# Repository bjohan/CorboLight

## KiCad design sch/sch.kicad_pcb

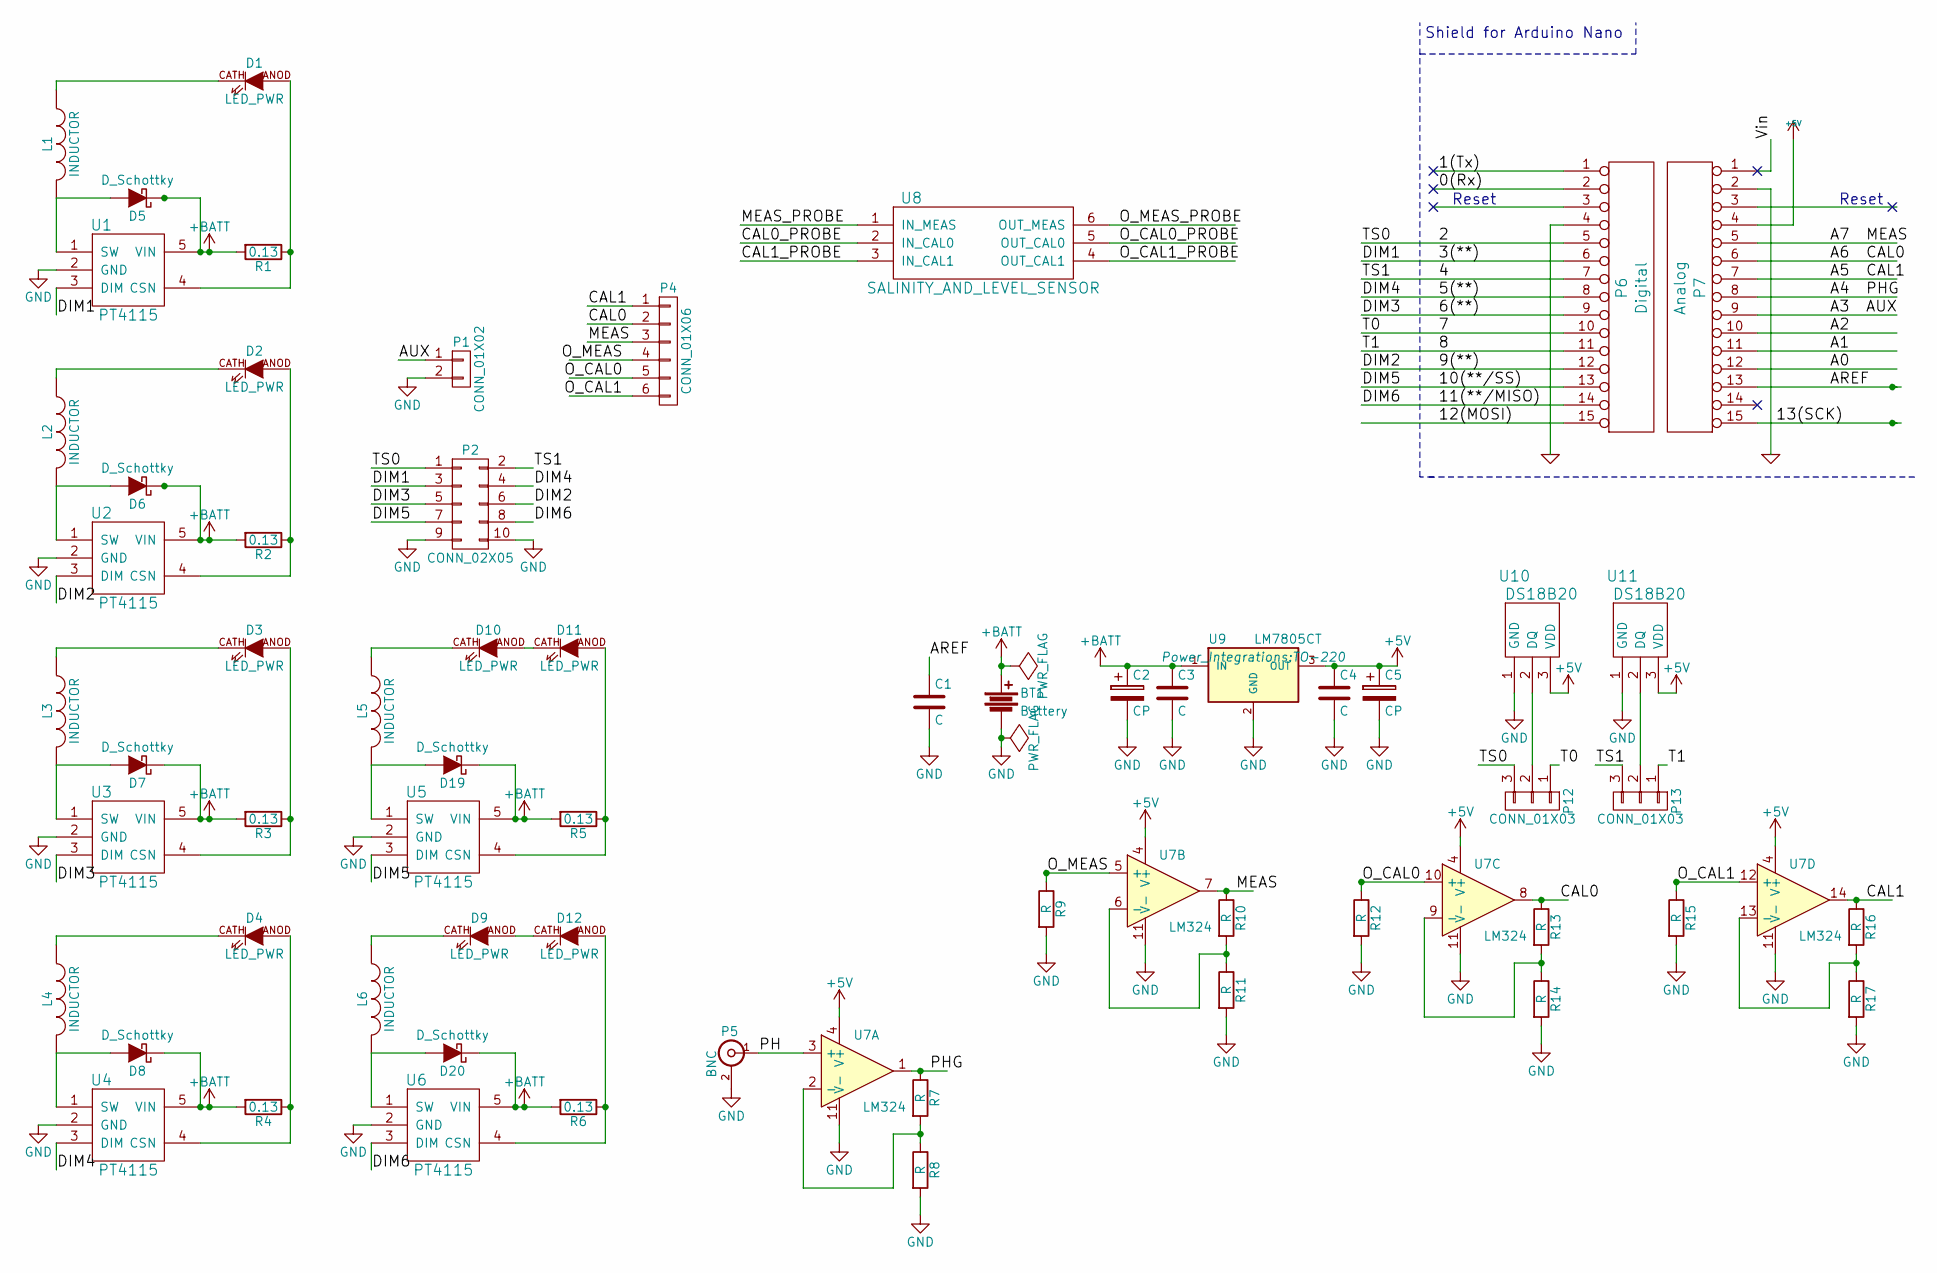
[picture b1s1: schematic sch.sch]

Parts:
BT1: Battery; bornier2
C1, C3, C4: C; C_1206_HandSoldering
C2, C5: CP; C_Radial_D5_L6_P2.5
D1, D2, D3, D4, D9, D10, D11, D12: LED_PWR; lumiled-2-LAMBERTIAN
D5, D6, D7, D8, D19, D20: D_Schottky; DO-214AB_Handsoldering
L1, L2, L3, L4, L5, L6: INDUCTOR; Neosid_Inductor_Ms95
P1: CONN_01X02; PINHEAD1-2
P2: CONN_02X05; IDC_Header_Straight_10pins
P4: CONN_01X06; PINHEAD1-6
P5: BNC; bnc-ci
P6: Digital; Socket_Strip_Arduino_1x15
P7: Analog; Socket_Strip_Arduino_1x15
P12, P13: CONN_01X03; PINHEAD1-3
R1, R2, R3, R4, R5, R6: 0.13; R_1206_HandSoldering
R7, R8, R9, R10, R11, R12, R13, R14, R15, R16, R17: R; R_0805_HandSoldering
U1, U2, U3, U4, U5, U6: PT4115; SOT89-5_Housing_Handsoldering
U7: LM324; SOIC-14_N
U8: SALINITY_AND_LEVEL_SENSOR
U9: LM7805CT; TO-220
U10, U11: DS18B20; TO-92_Inline_Narrow_Oval

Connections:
+5V: C4.1, C5.1, P7.4, U7.4 (V+), U9.3 (OUT), U10.3 (VDD), U11.3 (VDD)
+BATT: BT1.1, C2.1, C3.1, D5.1 (K), D6.1 (K), D7.1 (K), D8.1 (K), D19.1 (K), D20.1 (K), R1.2, R2.2, R3.2, R4.2, R5.2, R6.2, U1.5 (VIN), U2.5 (VIN), U3.5 (VIN), U4.5 (VIN), U5.5 (VIN), U6.5 (VIN), U9.1 (IN)
/0(Rx): P6.2
/1(Tx): P6.1
/2: P2.1, P6.5, P12.3
/3(**): P2.3, P6.6, U1.3 (DIM)
/4: P2.2, P6.7, P13.3
/5(**): P2.4, P6.8, U4.3 (DIM)
/6(**): P2.5, P6.9, U3.3 (DIM)
/7: P6.10, P12.1
/8: P6.11, P13.1
/9(**): P2.6, P6.12, U2.3 (DIM)
/10(**/SS): P2.7, P6.13, U5.3 (DIM)
/11(**/MISO): P2.8, P6.14, U6.3 (DIM)
/12(MOSI): P6.15 (p15)
/13(SCK): P7.15 (p15)
/A0: P7.12
/A1: P7.11
/A2: P7.10
/A3: P1.1, P7.9
/A4: P7.8, R7.1, U7.1
/A5: P4.1, P7.7, R16.1, U7.14
/A6: P4.2, P7.6, R13.1, U7.8
/A7: P4.3, P7.5, R10.1, U7.7
/AREF: C1.1, P7.13
/O_CAL0: P4.5, R12.1, U7.10 (+)
/O_CAL1: P4.6, R15.1, U7.12 (+)
/O_MEAS: P4.4, R9.1, U7.5 (+)
/PH: P5.1 (In), U7.3 (+)
/Vin: P7.1
GND: BT1.2, C1.2, C2.2, C3.2, C4.2, C5.2, P1.2, P2.9, P2.10, P5.2 (Ext), P6.4, P7.2, R8.2, R9.2, R11.2, R12.2, R14.2, R15.2, R17.2, U1.2 (GND), U2.2 (GND), U3.2 (GND), U4.2 (GND), U5.2 (GND), U6.2 (GND), U7.11 (V-), U9.2 (GND), U10.1 (GND), U11.1 (GND)
unnamed: D1.ANOD (A), R1.1, U1.4 (CSN)
unnamed: D1.CATH (C), L1.1
unnamed: D2.ANOD (A), R2.1, U2.4 (CSN)
unnamed: D2.CATH (C), L2.1
unnamed: D3.ANOD (A), R3.1, U3.4 (CSN)
unnamed: D3.CATH (C), L3.1
unnamed: D4.ANOD (A), R4.1, U4.4 (CSN)
unnamed: D4.CATH (C), L4.1
unnamed: D5.2 (A), L1.2, U1.1 (SW)
unnamed: D6.2 (A), L2.2, U2.1 (SW)
unnamed: D7.2 (A), L3.2, U3.1 (SW)
unnamed: D8.2 (A), L4.2, U4.1 (SW)
unnamed: D9.CATH (C), L6.1
unnamed: D10.ANOD (A), D11.CATH (C)
unnamed: D10.CATH (C), L5.1
unnamed: D11.ANOD (A), R5.1, U5.4 (CSN)
unnamed: D12.ANOD (A), R6.1, U6.4 (CSN)
unnamed: D9.ANOD (A), D12.CATH (C)
unnamed: D19.2 (A), L5.2, U5.1 (SW)
unnamed: D20.2 (A), L6.2, U6.1 (SW)
unnamed: P12.2, U10.2 (DQ)
unnamed: P13.2, U11.2 (DQ)
unnamed: R7.2, R8.1, U7.2 (-)
unnamed: R10.2, R11.1, U7.6 (-)
unnamed: R13.2, R14.1, U7.9 (-)
unnamed: R16.2, R17.1, U7.13 (-)

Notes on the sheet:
Shield for Arduino Nano
Reset

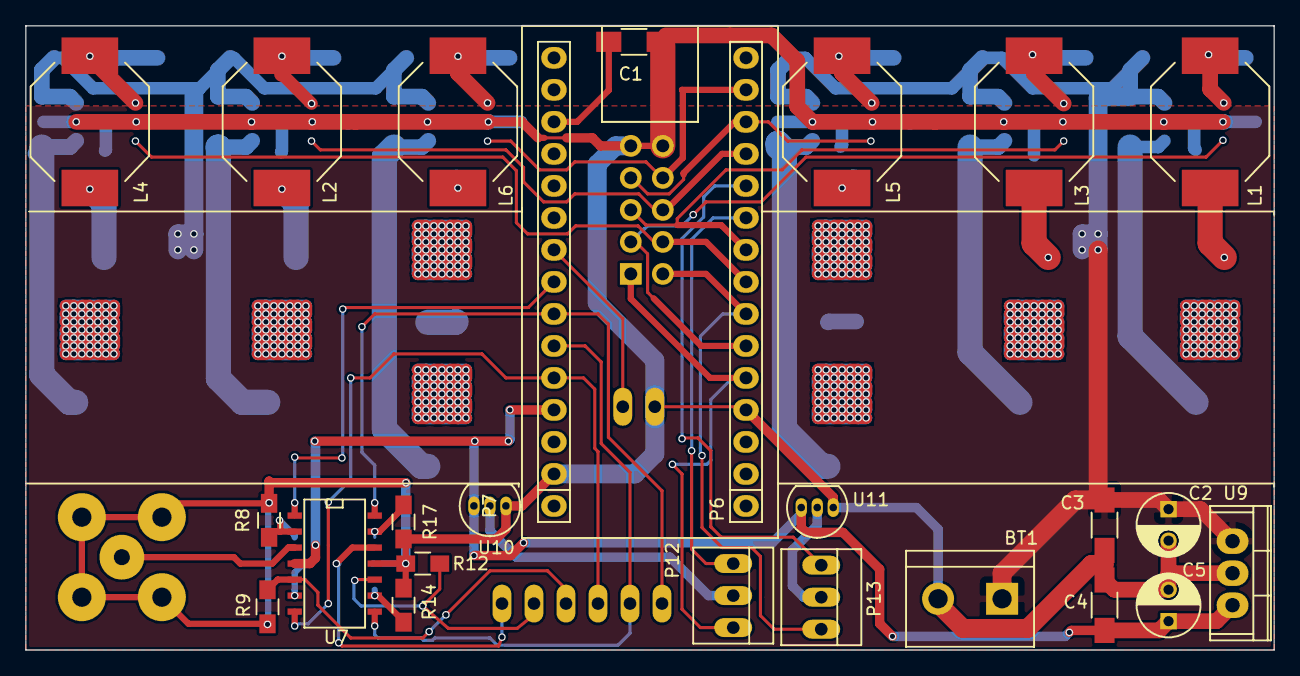
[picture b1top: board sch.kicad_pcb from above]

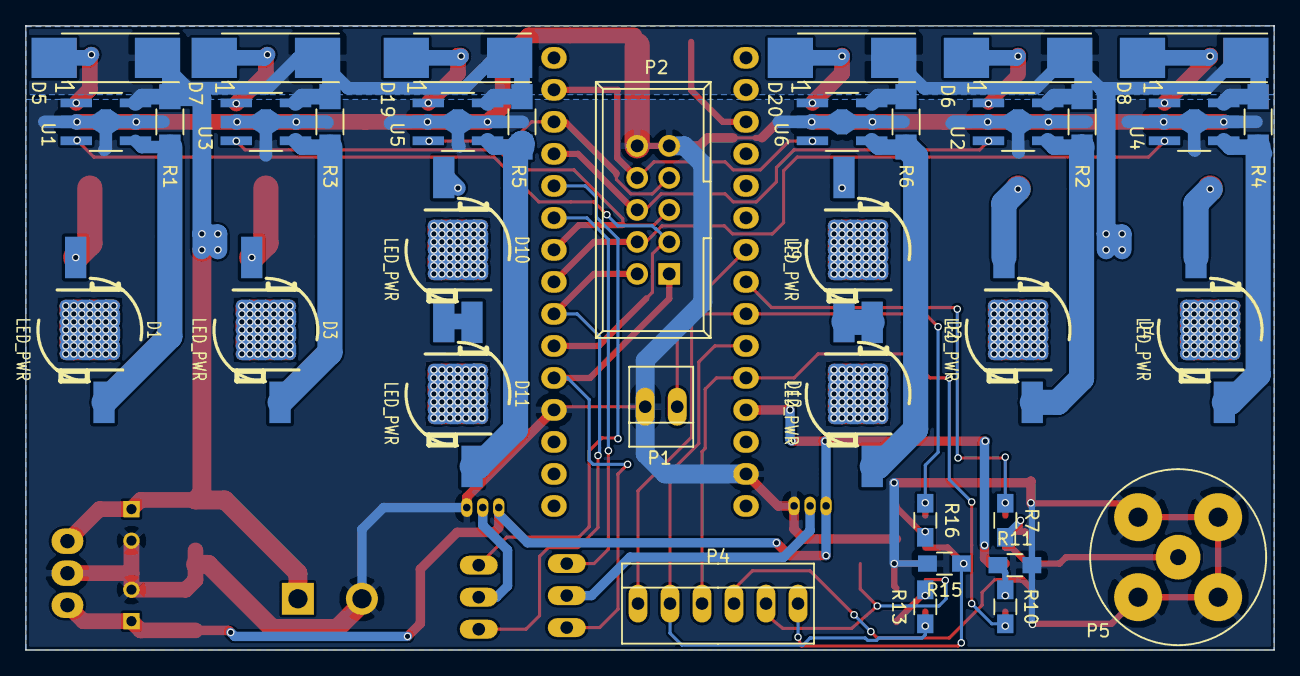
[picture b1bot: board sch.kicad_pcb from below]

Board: 2 copper layers, 99.1 x 49.5 mm, 61 parts (36 on the bottom side), 49 nets.

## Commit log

2016-07-23 Added system diagram
2016-07-23 Started kicad project
2016-07-23 Started schematic draft
2016-07-23 More schematic work
2016-07-24 Finished drafting and started correcting DRC
2016-07-24 Schematic ready for layout, started layout work
2016-07-26 Started placement
2016-07-27 Added some footprint libraries and started layout
2016-08-15 continued routing
2016-08-16 Changed some connections to make layout easier
2016-08-17 Initial version done
2016-08-17 Some minor fixes
2016-09-03 Fixed silkscreen and moved bnc connector so that silkscreen is on the board
2016-09-04 Fixed minor details in pcb and added openings in solder mas for thermal vias behind led
2016-09-23 Simple firmware to dim leds
2016-10-08 Added first version of housing
2016-11-30 Added load and save funktions for led power levels
2016-12-08 Added code for reading dallas
2016-12-11 Added fixed bug introduced earlier some time with caching values. Also tested ph probe
2016-12-15 Experiments with printing
2016-12-25 started work on pcb mounting
2016-12-25 Added clamps for pcb
2016-12-25 Added holes for mounting
